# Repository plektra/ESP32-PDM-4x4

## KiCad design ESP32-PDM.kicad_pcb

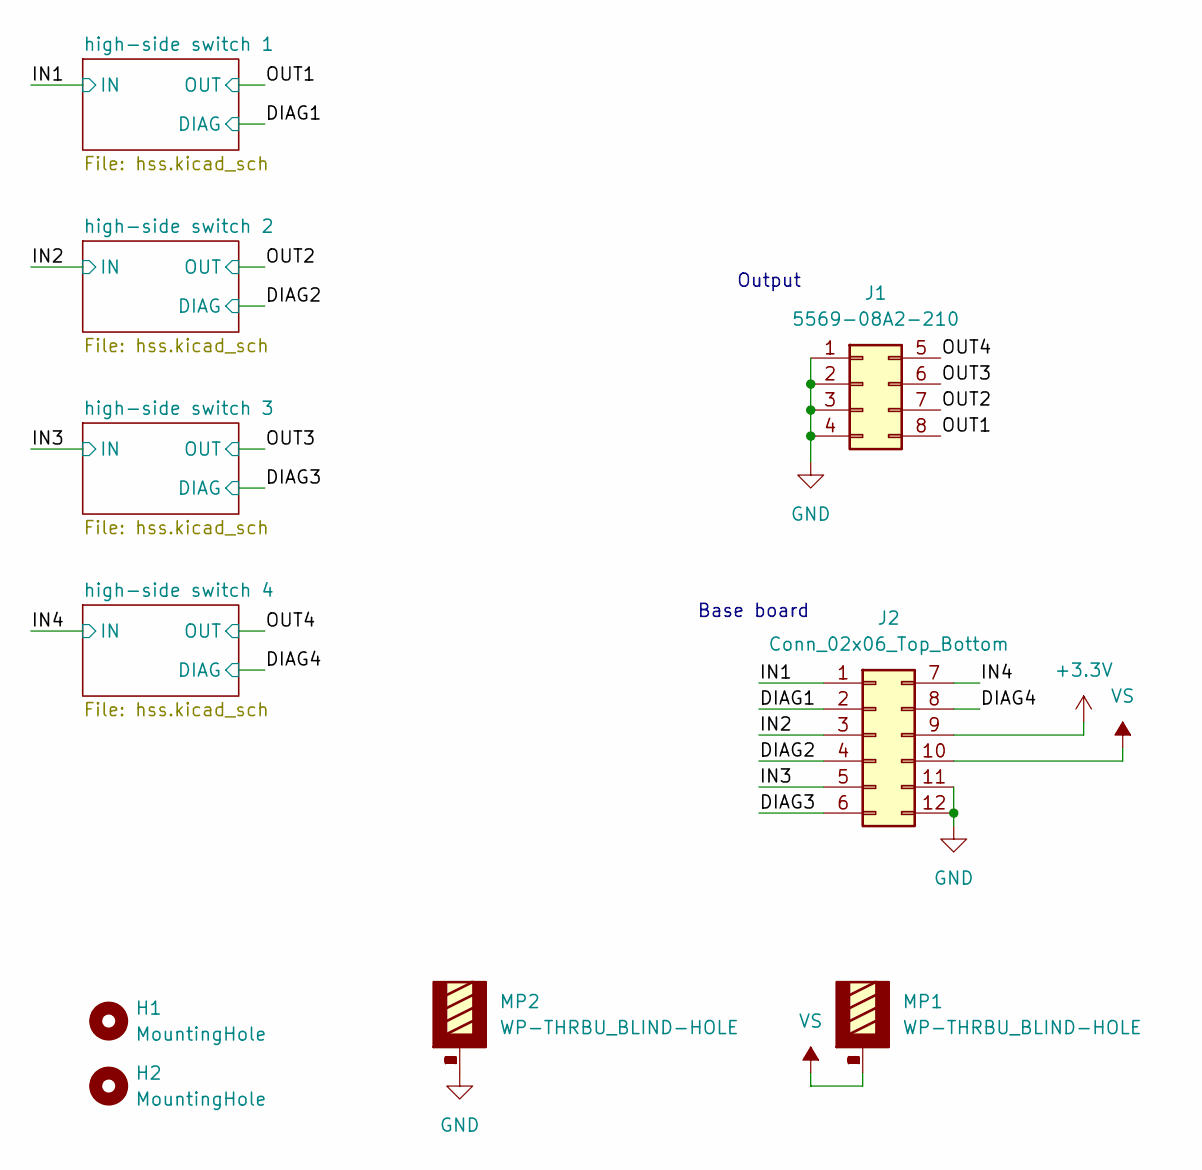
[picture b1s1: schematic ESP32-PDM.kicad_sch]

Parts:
H1, H2: MountingHole; MountingHole_3mm
J1: 5569-08A2-210; Molex_Mini-Fit_Jr_5569-08A2_2x04_P4.20mm_Horizontal
J2: Conn_02x06_Top_Bottom; PinHeader_2x06_P2.54mm_Vertical
MP1, MP2: WP-THRBU_BLIND-HOLE; WP-THRBU_74650195; PART-NUMBER 74650195R

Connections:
+3.3V: J2.9; also elsewhere on the board
/DIAG1: J2.2; also elsewhere on the board
/DIAG2: J2.4; also elsewhere on the board
/DIAG3: J2.6; also elsewhere on the board
/DIAG4: J2.8; also elsewhere on the board
/IN1: J2.1; also elsewhere on the board
/IN2: J2.3; also elsewhere on the board
/IN3: J2.5; also elsewhere on the board
/IN4: J2.7; also elsewhere on the board
/OUT1: J1.8; also elsewhere on the board
/OUT2: J1.7; also elsewhere on the board
/OUT3: J1.6; also elsewhere on the board
/OUT4: J1.5; also elsewhere on the board
GND: J1.1, J1.2, J1.3, J1.4, J2.11, J2.12, MP2.1, MP2.2, MP2.3, MP2.4, MP2.5, MP2.6, MP2.7, MP2.8, MP2.9; also elsewhere on the board
VS: J2.10, MP1.1, MP1.2, MP1.3, MP1.4, MP1.5, MP1.6, MP1.7, MP1.8, MP1.9; also elsewhere on the board

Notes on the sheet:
Output
Base board

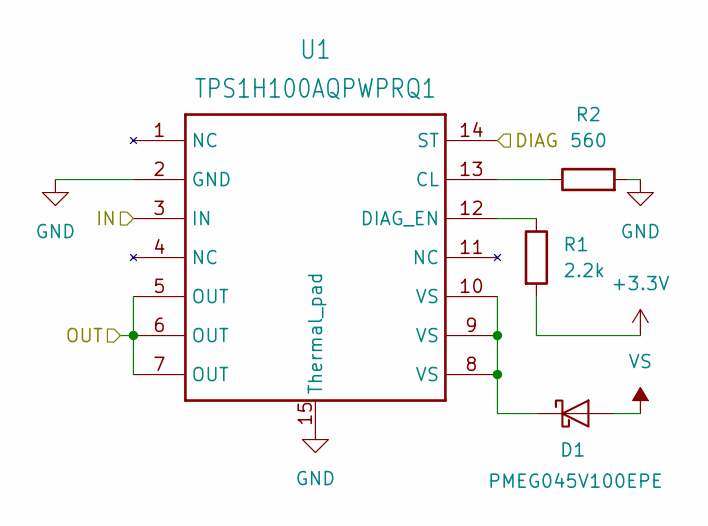
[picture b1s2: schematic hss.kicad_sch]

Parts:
D1: PMEG045V100EPE; TO-277A
R1: 2.2k; R_0402_1005Metric
R2: 560; R_0402_1005Metric
U1: TPS1H100AQPWPRQ1; IC_TPS27S100BPWPR

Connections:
+3.3V: R1.2; also elsewhere on the board
/DIAG1: U1.14 (ST); also elsewhere on the board
/IN1: U1.3 (IN); also elsewhere on the board
/OUT1: U1.5 (OUT), U1.6 (OUT), U1.7 (OUT); also elsewhere on the board
GND: R2.2, U1.2 (GND), U1.15 (Thermal_pad); also elsewhere on the board
unnamed: D1.3 (K), U1.8 (VS), U1.9 (VS), U1.10 (VS)
unnamed: R2.1, U1.13 (CL)
unnamed: R1.1, U1.12 (DIAG_EN)
VS: D1.1 (A), D1.2 (A); also elsewhere on the board

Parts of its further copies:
D2, D3, D4: PMEG045V100EPE; TO-277A
R3, R5, R7: 2.2k; R_0402_1005Metric
R4, R6, R8: 560; R_0402_1005Metric
U2, U3, U4: TPS1H100AQPWPRQ1; IC_TPS27S100BPWPR

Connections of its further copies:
+3.3V: R3.2, R5.2, R7.2; also elsewhere on the board
/DIAG2: U2.14 (ST); also elsewhere on the board
/DIAG3: U3.14 (ST); also elsewhere on the board
/DIAG4: U4.14 (ST); also elsewhere on the board
/IN2: U2.3 (IN); also elsewhere on the board
/IN3: U3.3 (IN); also elsewhere on the board
/IN4: U4.3 (IN); also elsewhere on the board
/OUT2: U2.5 (OUT), U2.6 (OUT), U2.7 (OUT); also elsewhere on the board
/OUT3: U3.5 (OUT), U3.6 (OUT), U3.7 (OUT); also elsewhere on the board
/OUT4: U4.5 (OUT), U4.6 (OUT), U4.7 (OUT); also elsewhere on the board
GND: R4.2, R6.2, R8.2, U2.2 (GND), U2.15 (Thermal_pad), U3.2 (GND), U3.15 (Thermal_pad), U4.2 (GND), U4.15 (Thermal_pad); also elsewhere on the board
unnamed: D2.3 (K), U2.8 (VS), U2.9 (VS), U2.10 (VS)
unnamed: D3.3 (K), U3.8 (VS), U3.9 (VS), U3.10 (VS)
unnamed: D4.3 (K), U4.8 (VS), U4.9 (VS), U4.10 (VS)
unnamed: R4.1, U2.13 (CL)
unnamed: R3.1, U2.12 (DIAG_EN)
unnamed: R6.1, U3.13 (CL)
unnamed: R5.1, U3.12 (DIAG_EN)
unnamed: R8.1, U4.13 (CL)
unnamed: R7.1, U4.12 (DIAG_EN)
VS: D2.1 (A), D2.2 (A), D3.1 (A), D3.2 (A), D4.1 (A), D4.2 (A); also elsewhere on the board

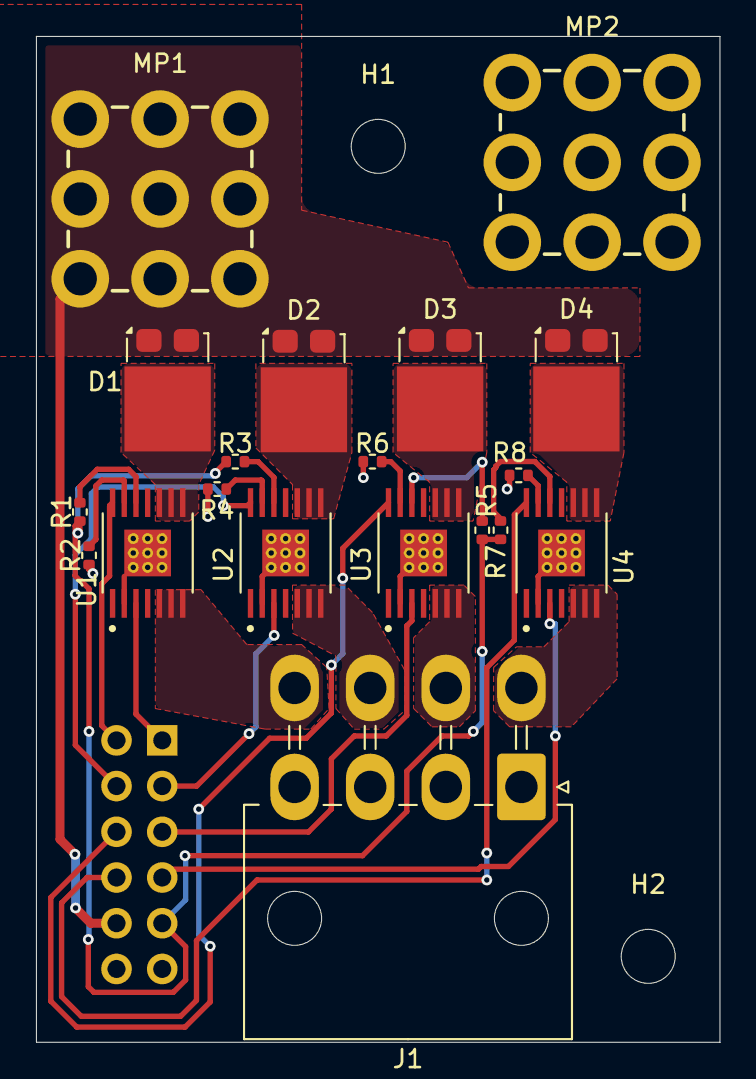
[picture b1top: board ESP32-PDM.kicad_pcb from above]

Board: 2 copper layers, 38.0 x 55.9 mm, 22 parts (1 on the bottom side), 27 nets.

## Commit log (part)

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2025-01-17 initial schematic draft
2025-02-06 PCB first version
